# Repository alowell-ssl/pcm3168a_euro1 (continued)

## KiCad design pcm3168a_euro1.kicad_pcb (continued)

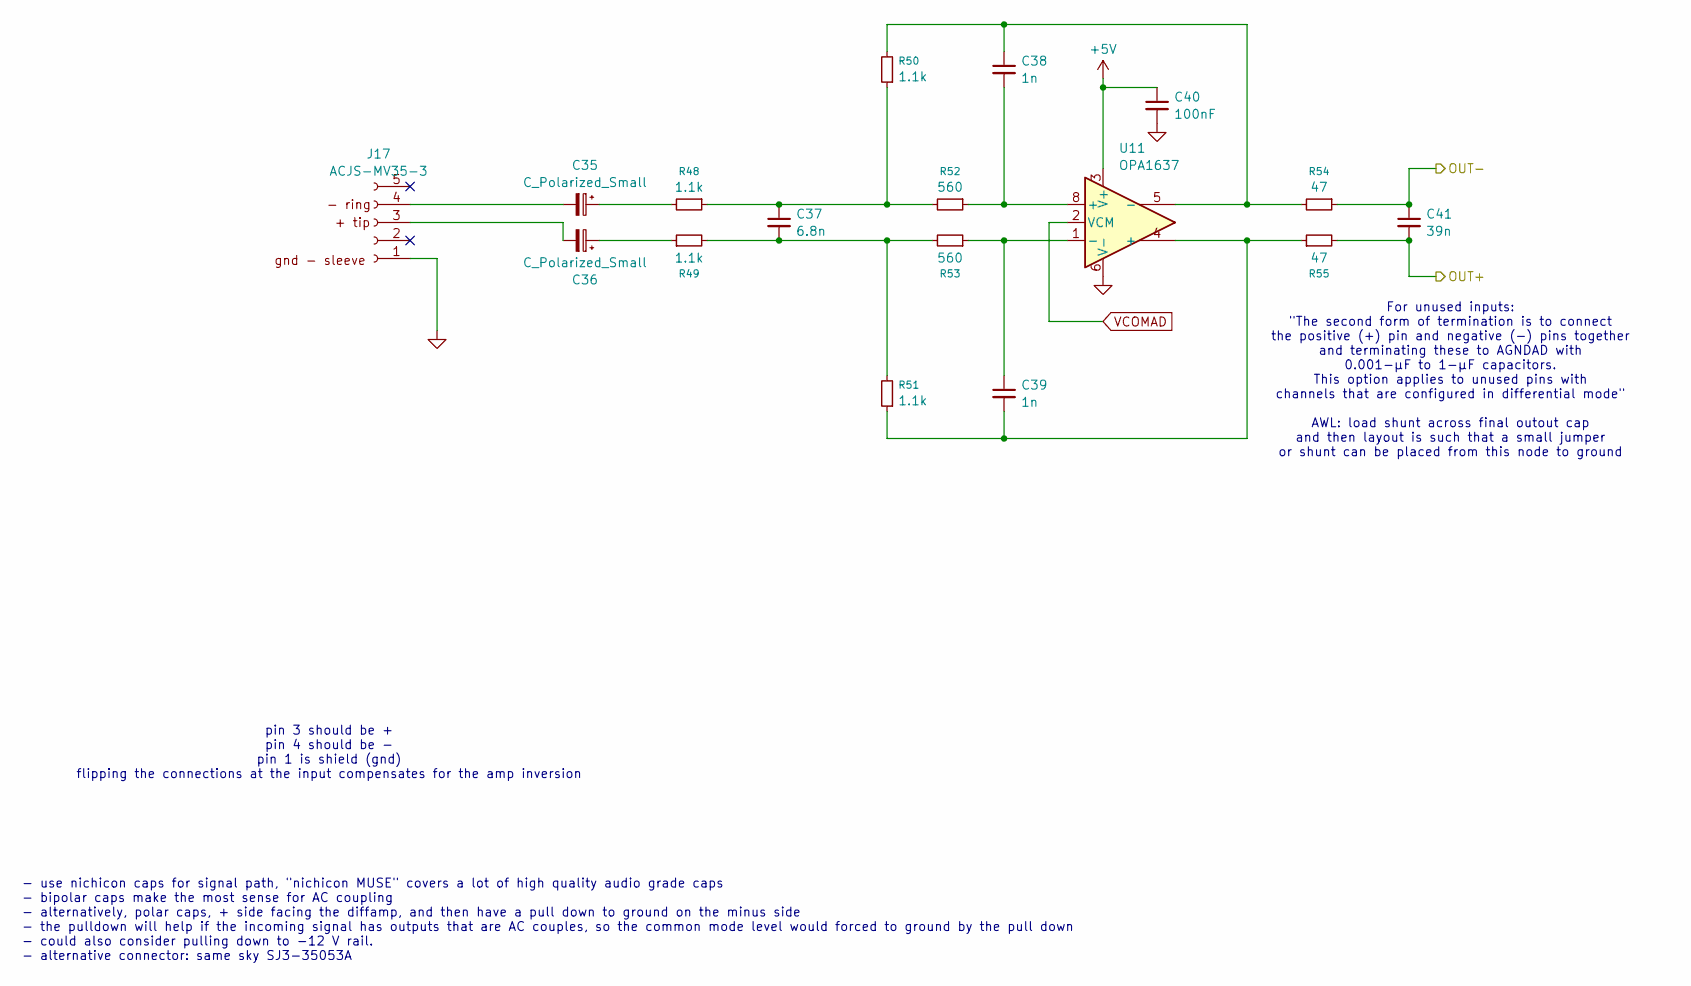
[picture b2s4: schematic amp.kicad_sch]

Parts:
C35, C36: C_Polarized_Small; CP_Radial_D8.0mm_P3.50mm
C37: 6.8n; C_0603_1608Metric
C38, C39: 1n; C_0603_1608Metric
C40: 100nF; C_0603_1608Metric
C41: 39n; C_0603_1608Metric
J17: ACJS-MV35-3; Amphenol_ACJS
R48, R49, R50, R51: 1.1k; R_0603_1608Metric
R52, R53: 560; R_0603_1608Metric
R54, R55: 47; R_0603_1608Metric
U11: OPA1637; SOIC-8_3.9x4.9mm_P1.27mm

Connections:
+5V: C40.1, U11.3 (V+); also elsewhere on the board
/VIN2+: C41.2, R55.2; also elsewhere on the board
/VIN2-: C41.1, R54.1; also elsewhere on the board
GND: C40.2, J17.1, U11.6 (V-); also elsewhere on the board
unnamed: C35.1, R48.2
unnamed: C36.1, R49.1
unnamed: C37.1, R48.1, R50.1, R52.2
unnamed: C37.2, R49.2, R51.2, R53.2
unnamed: C38.1, R50.2, R54.2, U11.5 (-)
unnamed: C38.2, R52.1, U11.8 (+)
unnamed: C39.1, R53.1, U11.1 (-)
unnamed: C39.2, R51.1, R55.1, U11.4 (+)
unnamed: C36.2, J17.3
unnamed: C35.2, J17.4
VCOMAD: U11.2 (VCM); also elsewhere on the board

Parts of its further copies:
C31, C67, C73, C74, C80, C81: C_Polarized_Small; CP_Radial_D8.0mm_P3.50mm
C32, C70, C76, C77, C83, C84: 1n; C_0603_1608Metric
C68, C75, C82: 6.8n; C_0603_1608Metric
C71, C78, C85: 100nF; C_0603_1608Metric
C72, C79, C86: 39n; C_0603_1608Metric
J1, J21, J22: ACJS-MV35-3; Amphenol_ACJS
R2, R58, R59, R61, R66, R67, R68, R69, R74, R75, R76, R77: 1.1k; R_0603_1608Metric
R62, R63, R70, R71, R78, R79: 560; R_0603_1608Metric
R64, R65, R72, R73, R80, R81: 47; R_0603_1608Metric
U13, U14, U15: OPA1637; SOIC-8_3.9x4.9mm_P1.27mm

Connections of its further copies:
+5V: C71.1, C78.1, C85.1, U13.3 (V+), U14.3 (V+), U15.3 (V+); also elsewhere on the board
/VIN1+: C72.2, R65.2; also elsewhere on the board
/VIN1-: C72.1, R64.1; also elsewhere on the board
/VIN3+: C79.2, R73.2; also elsewhere on the board
/VIN3-: C79.1, R72.1; also elsewhere on the board
/VIN4+: C86.2, R81.2; also elsewhere on the board
/VIN4-: C86.1, R80.1; also elsewhere on the board
GND: C71.2, C78.2, C85.2, J1.1, J21.1, J22.1, U13.6 (V-), U14.6 (V-), U15.6 (V-); also elsewhere on the board
unnamed: C31.1, R58.2
unnamed: C32.1, R2.2, R64.2, U13.5 (-)
unnamed: C32.2, R62.1, U13.8 (+)
unnamed: C67.1, R59.1
unnamed: C68.1, R2.1, R58.1, R62.2
unnamed: C68.2, R59.2, R61.2, R63.2
unnamed: C70.1, R63.1, U13.1 (-)
unnamed: C70.2, R61.1, R65.1, U13.4 (+)
unnamed: C73.1, R66.2
unnamed: C74.1, R67.1
unnamed: C75.1, R66.1, R68.1, R70.2
unnamed: C75.2, R67.2, R69.2, R71.2
unnamed: C76.1, R68.2, R72.2, U14.5 (-)
unnamed: C76.2, R70.1, U14.8 (+)
unnamed: C77.1, R71.1, U14.1 (-)
unnamed: C77.2, R69.1, R73.1, U14.4 (+)
unnamed: C80.1, R74.2
unnamed: C81.1, R75.1
unnamed: C82.1, R74.1, R76.1, R78.2
unnamed: C82.2, R75.2, R77.2, R79.2
unnamed: C83.1, R76.2, R80.2, U15.5 (-)
unnamed: C83.2, R78.1, U15.8 (+)
unnamed: C84.1, R79.1, U15.1 (-)
unnamed: C84.2, R77.1, R81.1, U15.4 (+)
unnamed: C67.2, J1.3
unnamed: C31.2, J1.4
unnamed: C74.2, J21.3
unnamed: C73.2, J21.4
unnamed: C81.2, J22.3
unnamed: C80.2, J22.4
VCOMAD: U13.2 (VCM), U14.2 (VCM), U15.2 (VCM); also elsewhere on the board

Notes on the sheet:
For unused inputs: "The second form of termination is to connect the positive (+) pin and negative (-) pins together and terminating these to AGNDAD with 0.001-μF to 1-μF capacitors. This option applies to unused pins with channels that are configured in differential mode" AWL: load shunt across fi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
- use nichicon caps for signal path, "nichicon MUSE" covers a lot of high quality audio grade caps - bipolar caps make the most sense for AC coupling - alternatively, polar caps, + side facing the diffamp, and then have a pull down to ground on the minus side - the pulldown will help if the incomin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
pin 3 should be + pin 4 should be - pin 1 is shield (gnd) flipping the connections at the input compensates for the amp inversion

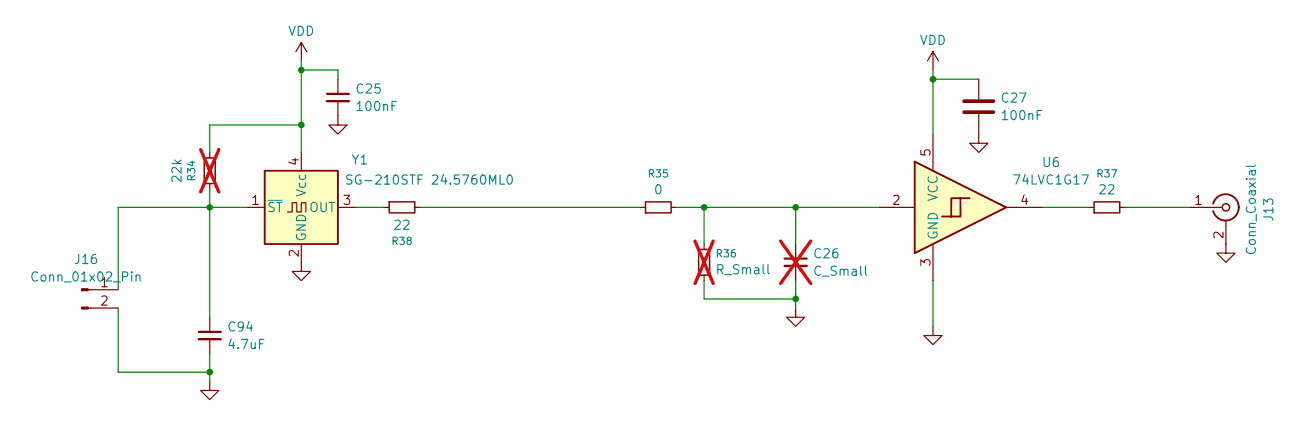
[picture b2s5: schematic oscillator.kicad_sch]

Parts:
C25, C27: 100nF; C_0603_1608Metric
C26: C_Small; C_0603_1608Metric; not fitted
C94: 4.7uF; C_0603_1608Metric
J13: Conn_Coaxial; SMA_Amphenol_901-144_Vertical
J16: Conn_01x02_Pin; PinHeader_1x02_P2.54mm_Vertical
R34: 22k; R_0603_1608Metric; not fitted
R35: 0; R_0603_1608Metric
R36: R_Small; R_0603_1608Metric; not fitted
R37, R38: 22; R_0603_1608Metric
U6: 74LVC1G17; SOT-23-5
Y1: SG-210STF 24.5760ML0; Oscillator_SMD_SeikoEpson_SG210-4Pin_2.5x2.0mm

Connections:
GND: C25.2, C26.2, C27.2, C94.2, J13.2 (Ext), J16.2, R36.1, U6.3 (GND), Y1.2 (GND); also elsewhere on the board
unnamed: C26.1, R35.2, R36.2, U6.2
unnamed: J13.1 (In), R37.2
unnamed: C94.1, J16.1, R34.2, Y1.1 (~ST)
unnamed: R35.1, R38.2
unnamed: R37.1, U6.4
unnamed: R38.1, Y1.3 (OUT)
VDD: C25.1, C27.1, R34.1, U6.5 (VCC), Y1.4 (Vcc); also elsewhere on the board

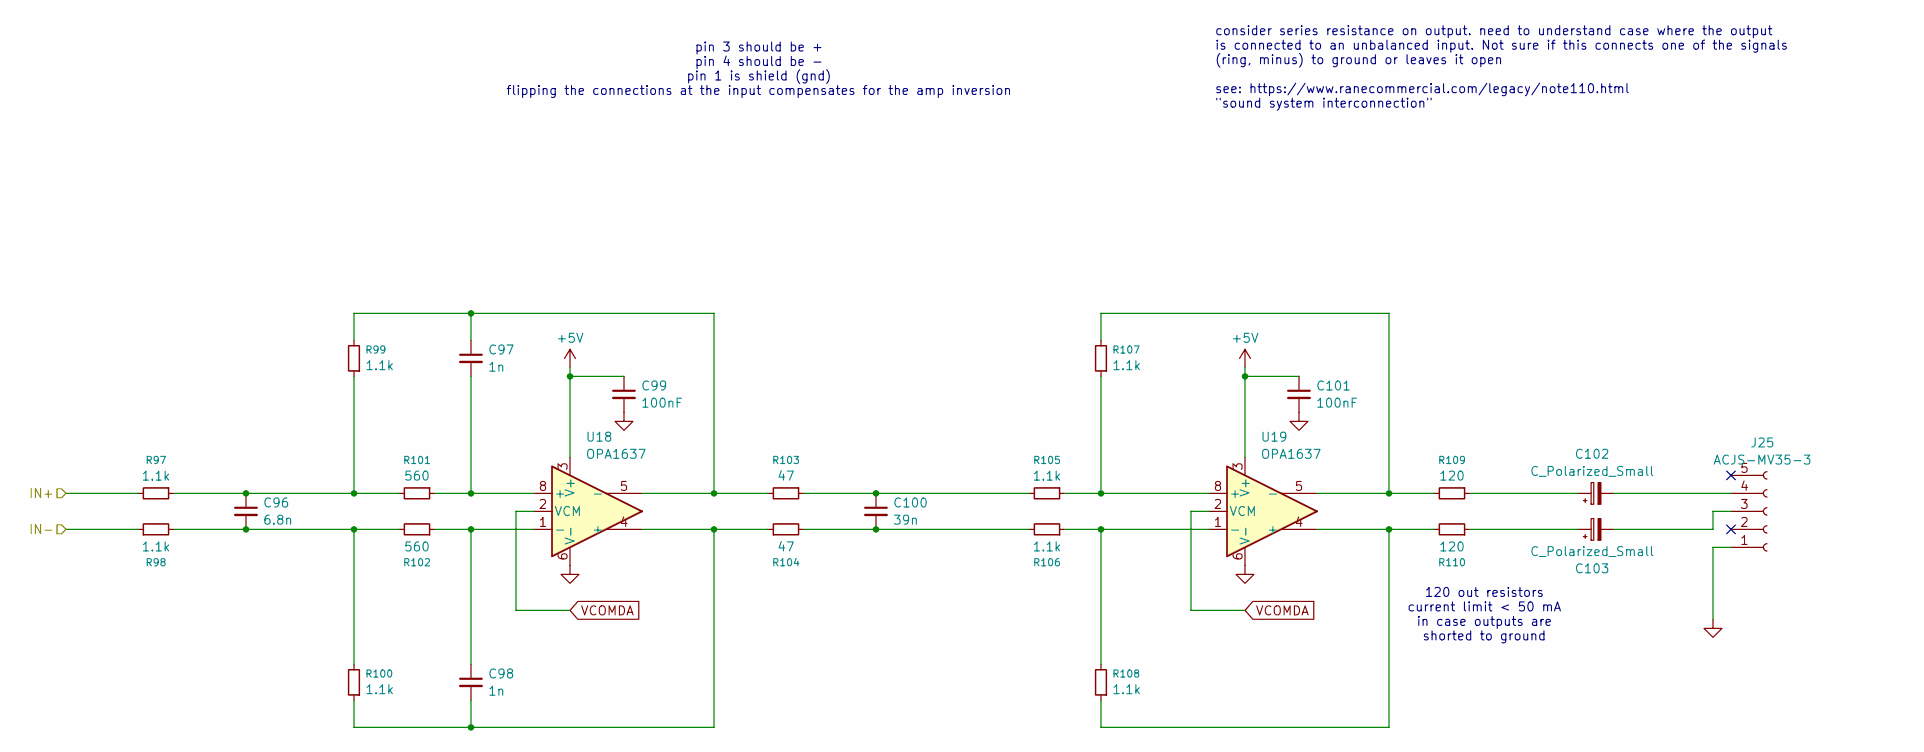
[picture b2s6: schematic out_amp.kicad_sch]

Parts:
C96: 6.8n; C_0603_1608Metric
C97, C98: 1n; C_0603_1608Metric
C99, C101: 100nF; C_0603_1608Metric
C100: 39n; C_0603_1608Metric
C102, C103: C_Polarized_Small; CP_Radial_D8.0mm_P3.50mm
J25: ACJS-MV35-3; Amphenol_ACJS
R97, R98, R99, R100, R105, R106, R107, R108: 1.1k; R_0603_1608Metric
R101, R102: 560; R_0603_1608Metric
R103, R104: 47; R_0603_1608Metric
R109, R110: 120; R_0603_1608Metric
U18, U19: OPA1637; SOIC-8_3.9x4.9mm_P1.27mm

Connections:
+5V: C99.1, C101.1, U18.3 (V+), U19.3 (V+); also elsewhere on the board
/VOUT2+: R97.2; also elsewhere on the board
/VOUT2-: R98.1; also elsewhere on the board
GND: C99.2, C101.2, J25.1, U18.6 (V-), U19.6 (V-); also elsewhere on the board
unnamed: C96.1, R97.1, R99.1, R101.2
unnamed: C96.2, R98.2, R100.2, R102.2
unnamed: C97.1, R99.2, R103.2, U18.5 (-)
unnamed: C97.2, R101.1, U18.8 (+)
unnamed: C98.1, R102.1, U18.1 (-)
unnamed: C98.2, R100.1, R104.1, U18.4 (+)
unnamed: C100.1, R103.1, R105.2
unnamed: C100.2, R104.2, R106.2
unnamed: C102.1, R109.1
unnamed: C103.1, R110.1
unnamed: C103.2, J25.3
unnamed: C102.2, J25.4
unnamed: R105.1, R107.1, U19.8 (+)
unnamed: R106.1, R108.2, U19.1 (-)
unnamed: R107.2, R109.2, U19.5 (-)
unnamed: R108.1, R110.2, U19.4 (+)
VCOMDA: U18.2 (VCM), U19.2 (VCM); also elsewhere on the board

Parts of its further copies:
C87, C88, C110, C111, C118, C119: C_Polarized_Small; CP_Radial_D8.0mm_P3.50mm
C89, C104, C112: 6.8n; C_0603_1608Metric
C90, C91, C105, C106, C113, C114: 1n; C_0603_1608Metric
C92, C95, C107, C109, C115, C117: 100nF; C_0603_1608Metric
C93, C108, C116: 39n; C_0603_1608Metric
J24, J26, J27: ACJS-MV35-3; Amphenol_ACJS
R82, R83, R84, R85, R91, R92, R93, R94, R111, R112, R113, R114, R119, R120, R121, R122, R125, R126, R127, R128, R133, R134, R135, R136: 1.1k; R_0603_1608Metric
R86, R87, R115, R116, R129, R130: 560; R_0603_1608Metric
R88, R89, R117, R118, R131, R132: 47; R_0603_1608Metric
R95, R96, R123, R124, R137, R138: 120; R_0603_1608Metric
U16, U17, U20, U21, U22, U23: OPA1637; SOIC-8_3.9x4.9mm_P1.27mm

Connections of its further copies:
+5V: C92.1, C95.1, C107.1, C109.1, C115.1, C117.1, U16.3 (V+), U17.3 (V+), U20.3 (V+), U21.3 (V+), U22.3 (V+), U23.3 (V+); also elsewhere on the board
/VOUT1+: R82.2; also elsewhere on the board
/VOUT1-: R83.1; also elsewhere on the board
/VOUT3+: R111.2; also elsewhere on the board
/VOUT3-: R112.1; also elsewhere on the board
/VOUT4+: R125.2; also elsewhere on the board
/VOUT4-: R126.1; also elsewhere on the board
GND: C92.2, C95.2, C107.2, C109.2, C115.2, C117.2, J24.1, J26.1, J27.1, U16.6 (V-), U17.6 (V-), U20.6 (V-), U21.6 (V-), U22.6 (V-), U23.6 (V-); also elsewhere on the board
unnamed: C87.1, R95.1
unnamed: C88.1, R96.1
unnamed: C89.1, R82.1, R84.1, R86.2
unnamed: C89.2, R83.2, R85.2, R87.2
unnamed: C90.1, R84.2, R88.2, U16.5 (-)
unnamed: C90.2, R86.1, U16.8 (+)
unnamed: C91.1, R87.1, U16.1 (-)
unnamed: C91.2, R85.1, R89.1, U16.4 (+)
unnamed: C93.1, R88.1, R93.2
unnamed: C93.2, R89.2, R94.2
unnamed: C104.1, R111.1, R113.1, R115.2
unnamed: C104.2, R112.2, R114.2, R116.2
unnamed: C105.1, R113.2, R117.2, U20.5 (-)
unnamed: C105.2, R115.1, U20.8 (+)
unnamed: C106.1, R116.1, U20.1 (-)
unnamed: C106.2, R114.1, R118.1, U20.4 (+)
unnamed: C108.1, R117.1, R119.2
unnamed: C108.2, R118.2, R120.2
unnamed: C110.1, R123.1
unnamed: C111.1, R124.1
unnamed: C112.1, R125.1, R127.1, R129.2
unnamed: C112.2, R126.2, R128.2, R130.2
unnamed: C113.1, R127.2, R131.2, U22.5 (-)
unnamed: C113.2, R129.1, U22.8 (+)
unnamed: C114.1, R130.1, U22.1 (-)
unnamed: C114.2, R128.1, R132.1, U22.4 (+)
unnamed: C116.1, R131.1, R133.2
unnamed: C116.2, R132.2, R134.2
unnamed: C118.1, R137.1
unnamed: C119.1, R138.1
unnamed: C88.2, J24.3
unnamed: C87.2, J24.4
unnamed: C111.2, J26.3
unnamed: C110.2, J26.4
unnamed: C119.2, J27.3
unnamed: C118.2, J27.4
unnamed: R91.1, R93.1, U17.8 (+)
unnamed: R91.2, R95.2, U17.5 (-)
unnamed: R92.1, R96.2, U17.4 (+)
unnamed: R92.2, R94.1, U17.1 (-)
unnamed: R119.1, R121.1, U21.8 (+)
unnamed: R120.1, R122.2, U21.1 (-)
unnamed: R121.2, R123.2, U21.5 (-)
unnamed: R122.1, R124.2, U21.4 (+)
unnamed: R133.1, R135.1, U23.8 (+)
unnamed: R134.1, R136.2, U23.1 (-)
unnamed: R135.2, R137.2, U23.5 (-)
unnamed: R136.1, R138.2, U23.4 (+)
VCOMDA: U16.2 (VCM), U17.2 (VCM), U20.2 (VCM), U21.2 (VCM), U22.2 (VCM), U23.2 (VCM); also elsewhere on the board

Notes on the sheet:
pin 3 should be + pin 4 should be - pin 1 is shield (gnd) flipping the connections at the input compensates for the amp inversion
consider series resistance on output. need to understand case where the output is connected to an unbalanced input. Not sure if this connects one of the signals (ring, minus) to ground or leaves it open see: https://www.ranecommercial.com/legacy/note110.html "sound system interconnection"
120 out resistors current limit < 50 mA in case outputs are shorted to ground

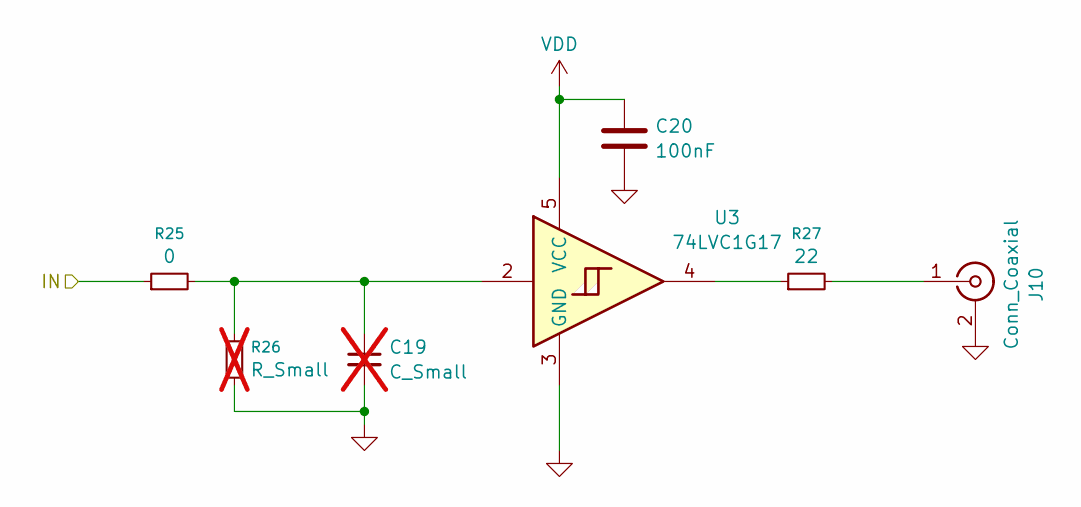
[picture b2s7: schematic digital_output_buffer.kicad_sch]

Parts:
C19: C_Small; C_0603_1608Metric; not fitted
C20: 100nF; C_0603_1608Metric
J10: Conn_Coaxial; SMA_Amphenol_901-144_Vertical
R25: 0; R_0603_1608Metric
R26: R_Small; R_0603_1608Metric; not fitted
R27: 22; R_0603_1608Metric
U3: 74LVC1G17; SOT-23-5

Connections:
/dout1/IN: R25.1; also elsewhere on the board
GND: C19.2, C20.2, J10.2 (Ext), R26.1, U3.3 (GND); also elsewhere on the board
unnamed: C19.1, R25.2, R26.2, U3.2
unnamed: J10.1 (In), R27.2
unnamed: R27.1, U3.4
VDD: C20.1, U3.5 (VCC); also elsewhere on the board

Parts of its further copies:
C23, C29, C33: C_Small; C_0603_1608Metric; not fitted
C24, C30, C34: 100nF; C_0603_1608Metric
J12, J14, J15: Conn_Coaxial; SMA_Amphenol_901-144_Vertical
R31, R39, R42: 0; R_0603_1608Metric
R32, R40, R43: R_Small; R_0603_1608Metric; not fitted
R33, R41, R44: 22; R_0603_1608Metric
U5, U8, U9: 74LVC1G17; SOT-23-5

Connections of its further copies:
/bck_master/IN: R39.1; also elsewhere on the board
/clk_in/OUT: R42.1; also elsewhere on the board
/lrck_master/IN: R31.1; also elsewhere on the board
GND: C23.2, C24.2, C29.2, C30.2, C33.2, C34.2, J12.2 (Ext), J14.2 (Ext), J15.2 (Ext), R32.1, R40.1, R43.1, U5.3 (GND), U8.3 (GND), U9.3 (GND); also elsewhere on the board
unnamed: C23.1, R31.2, R32.2, U5.2
unnamed: C29.1, R39.2, R40.2, U8.2
unnamed: C33.1, R42.2, R43.2, U9.2
unnamed: J12.1 (In), R33.2
unnamed: J14.1 (In), R41.2
unnamed: J15.1 (In), R44.2
unnamed: R33.1, U5.4
unnamed: R41.1, U8.4
unnamed: R44.1, U9.4
VDD: C24.1, C30.1, C34.1, U5.5 (VCC), U8.5 (VCC), U9.5 (VCC); also elsewhere on the board

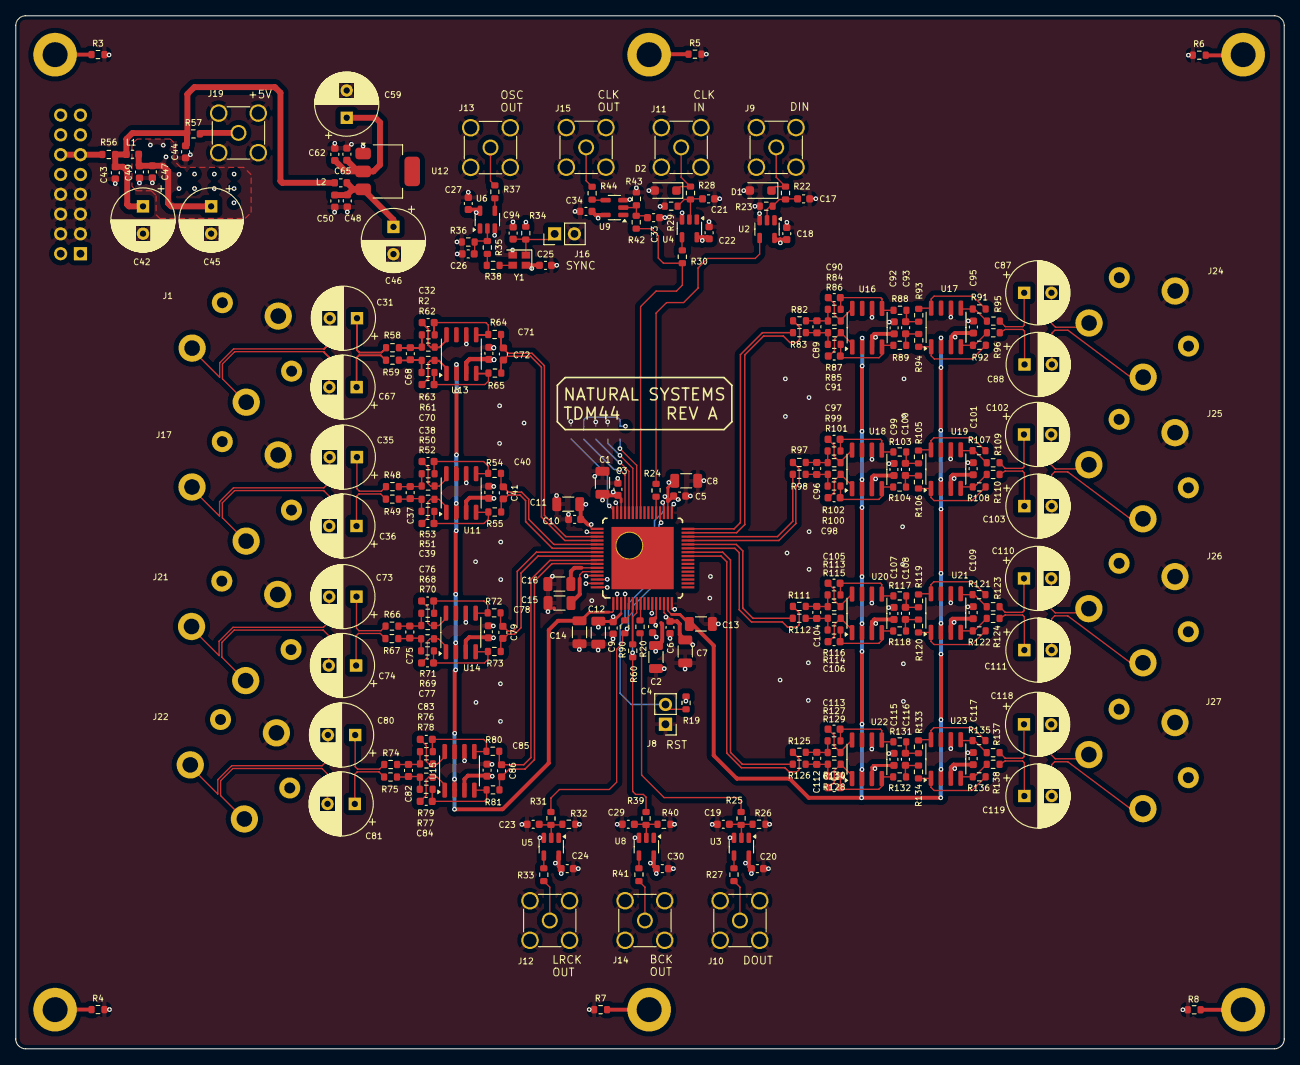
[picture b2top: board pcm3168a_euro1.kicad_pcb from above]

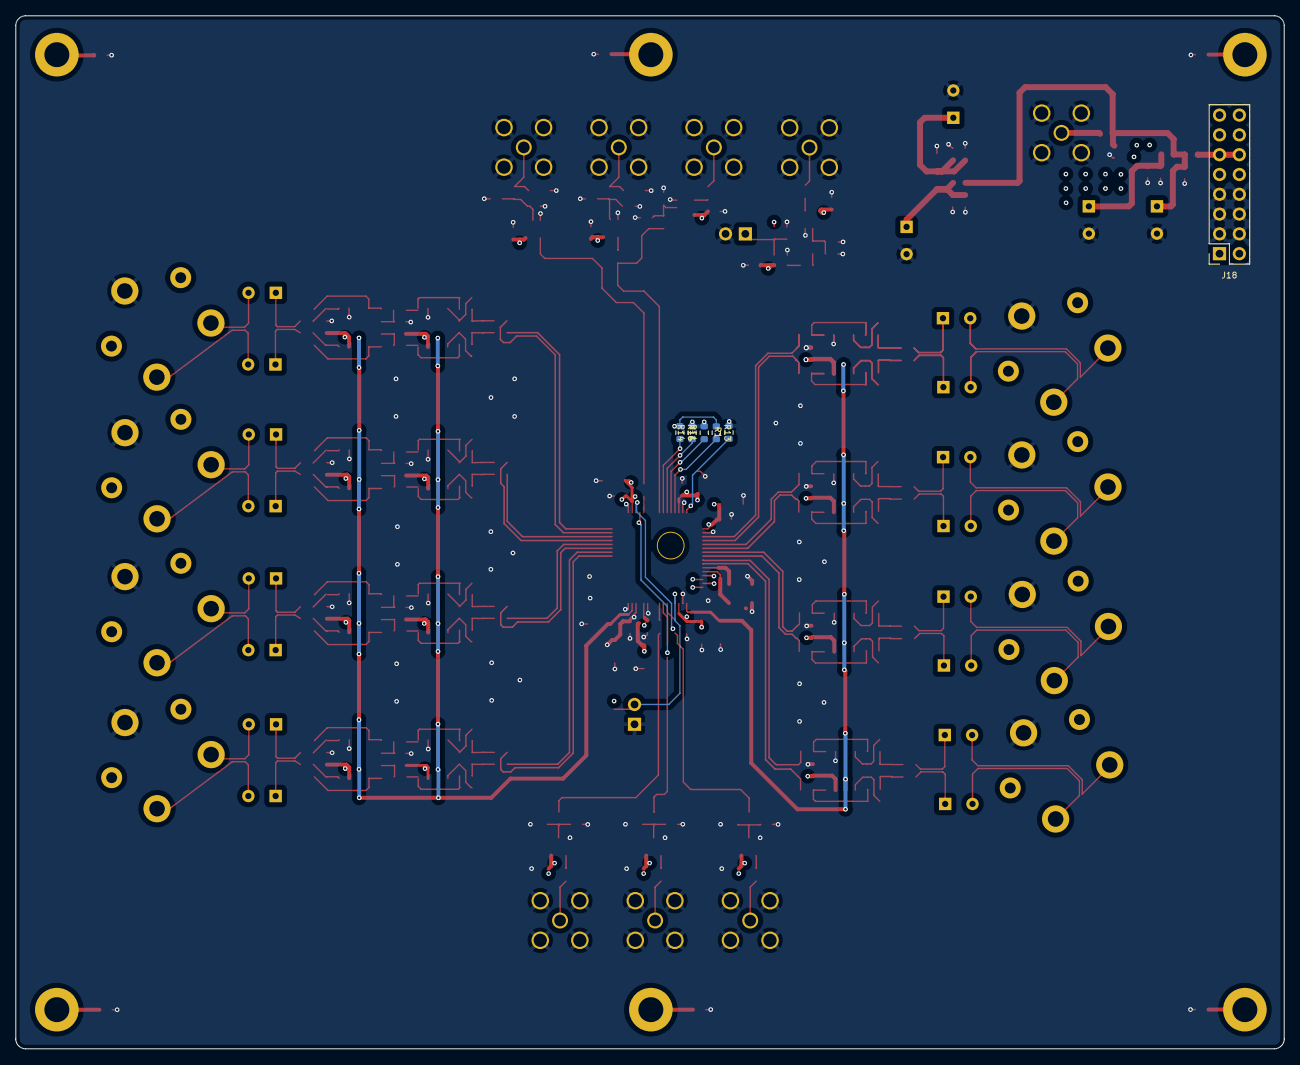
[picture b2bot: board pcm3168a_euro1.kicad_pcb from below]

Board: 4 copper layers, 162.7 x 132.5 mm, 283 parts (6 on the bottom side), 177 nets.

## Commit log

2025-06-01 starting to track on git. currently the board has stuff for running master or slave mode
2025-06-01 redoing file add
2025-06-01 commiting before making large changes. simplifying design, hard tying jumpers for more well defined operation modes. removing slave/slave capability, removing i2c
2025-06-07 WIP layout
2025-06-08 WIP: layout mostly done, everything connected and looking good. still have TODO list + DRC
2025-06-08 WIP need to fix OPA1637 footprint
2025-06-08 DONE. now exporting gerbers
2025-06-08 adding gerbers
2025-06-16 added part numbers
2025-06-27 trying to remove bad submodule
2025-06-27 adding support board, breakout for nucleo
2025-06-27 adding gerbers for TDM-b1
2025-06-28 filled out part number for tdm_b1
2025-06-29 started board for tdm 2 ethernet
